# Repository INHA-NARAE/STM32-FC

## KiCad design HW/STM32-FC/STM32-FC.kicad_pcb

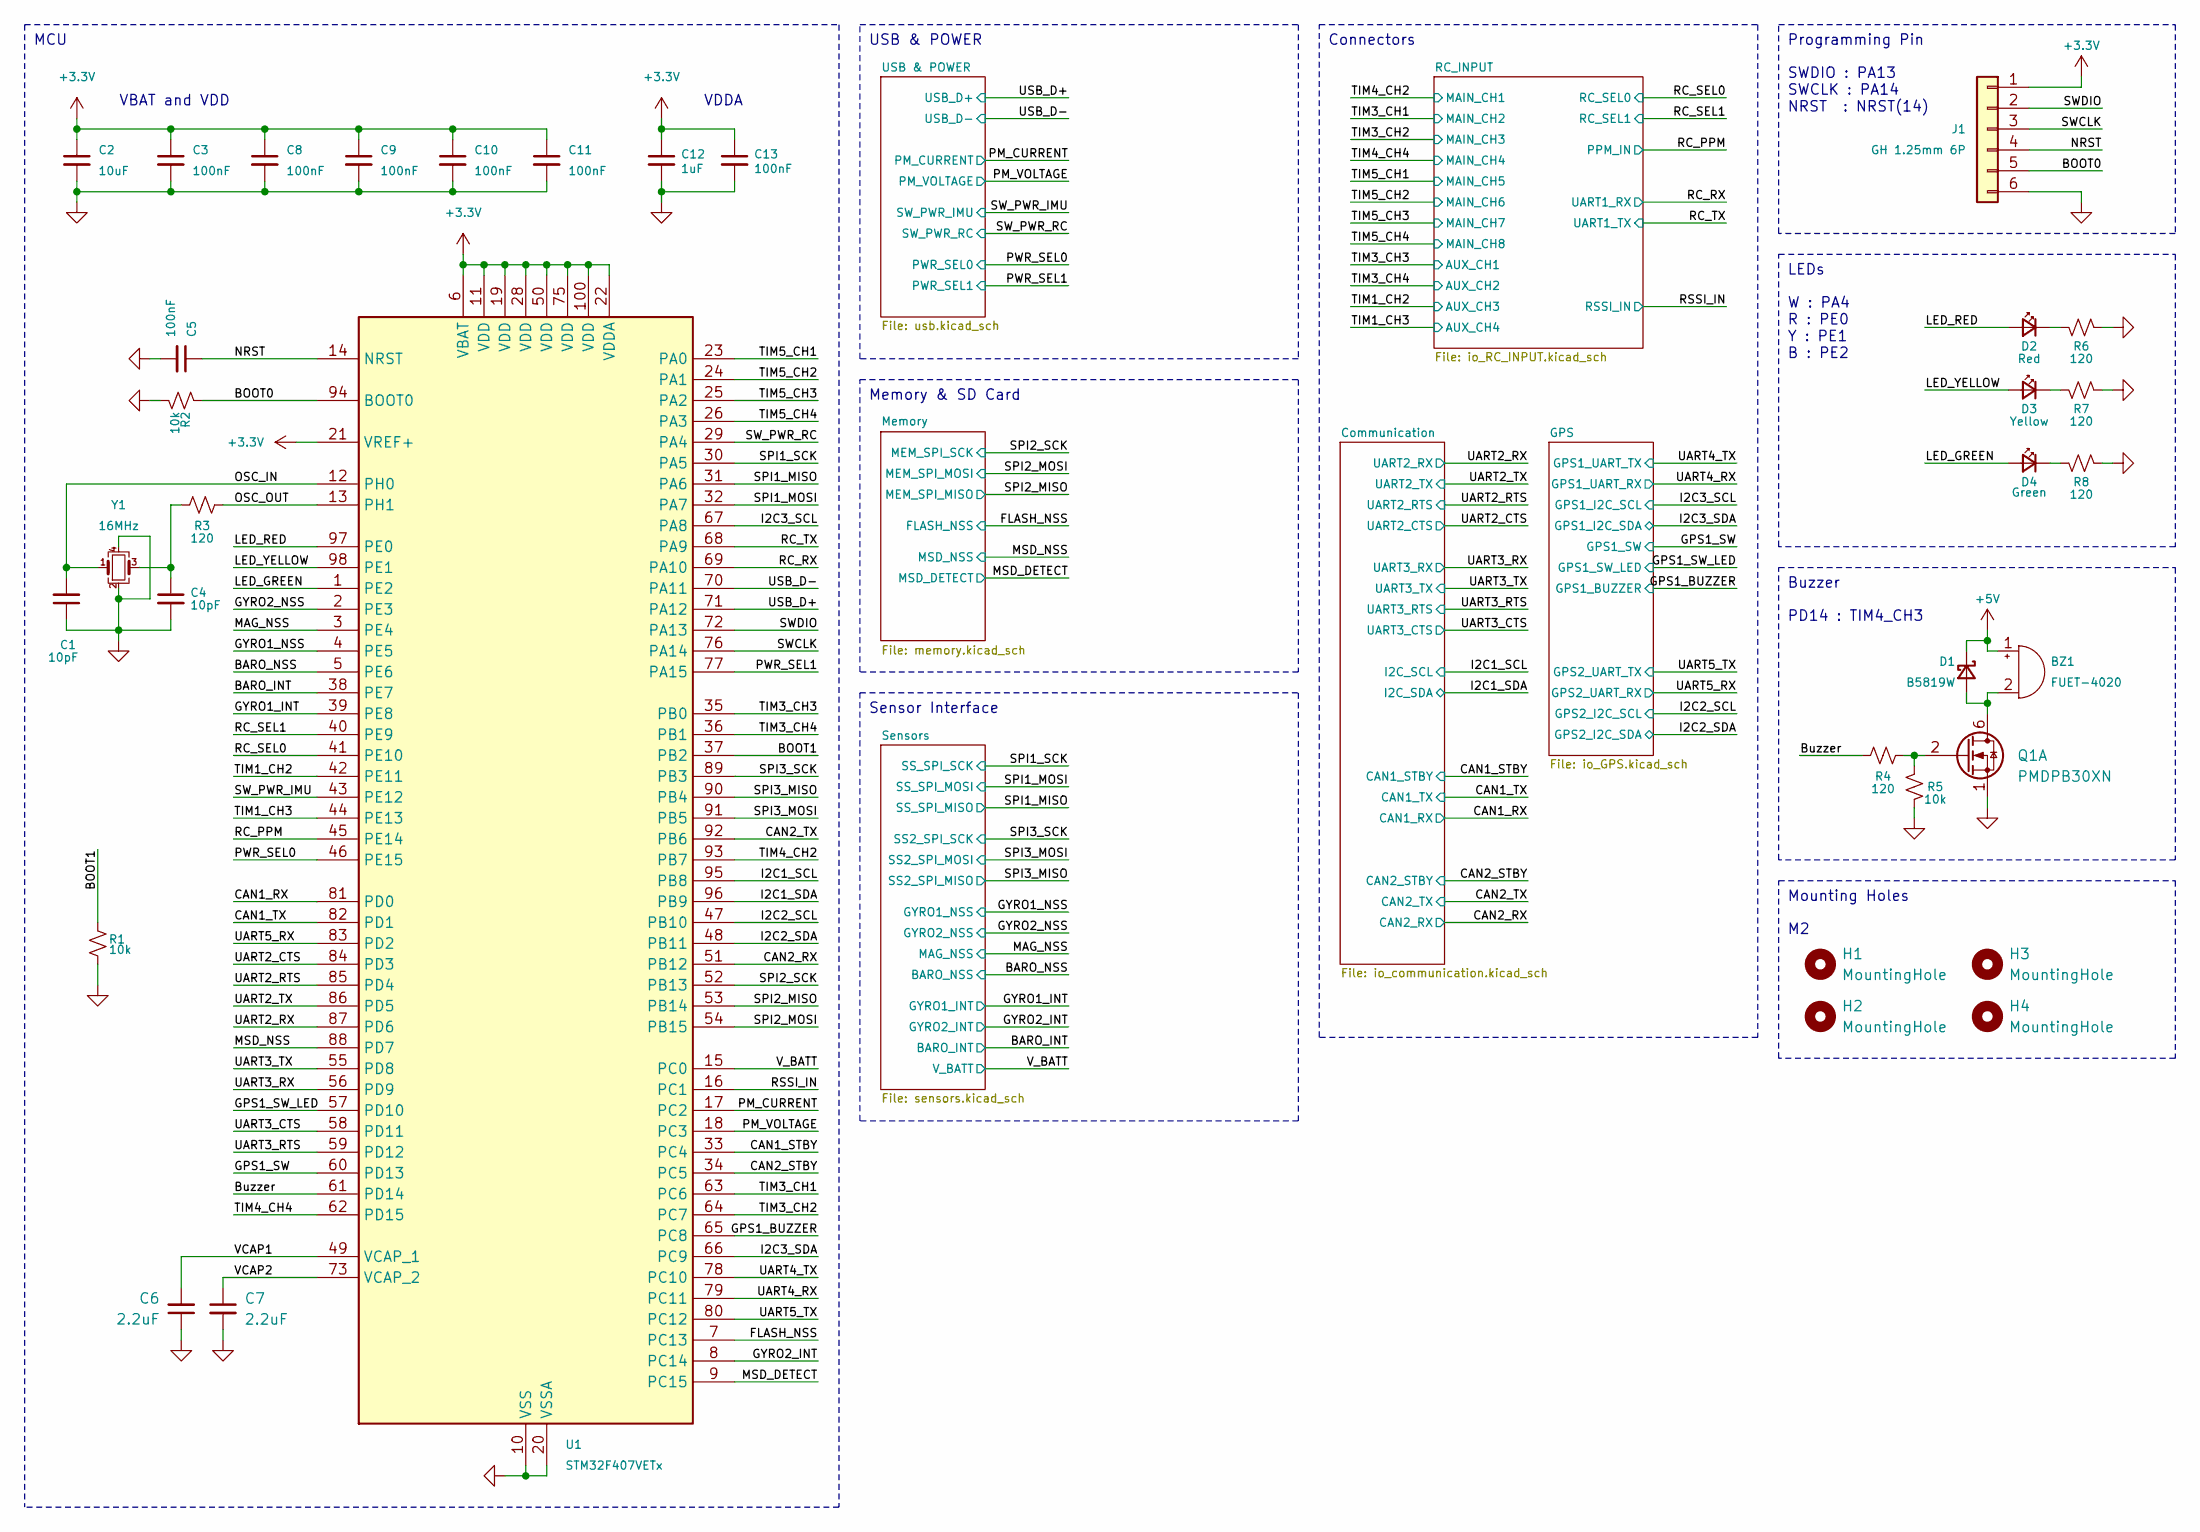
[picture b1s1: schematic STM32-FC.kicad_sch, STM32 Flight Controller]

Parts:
BZ1: FUET-4020; LCSC C391027
C1, C4: 10pF; C_0402_1005Metric; LCSC C1545
C2: 10uF; C_0402_1005Metric; LCSC C307415
C3, C5, C8, C9, C10, C11, C13: 100nF; C_0402_1005Metric; LCSC C1525
C6, C7: 2.2uF; C_0402_1005Metric; LCSC C170151
C12: 1uF; C_0402_1005Metric; LCSC C14445
D1: B5819W; D_SOD-323; LCSC C22624
D2: Red; LED_0402_1005Metric; LCSC C130719
D3: Yellow; LED_0402_1005Metric; LCSC C130721
D4: Green; LED_0402_1005Metric; LCSC C130722
H1, H2, H3, H4: MountingHole; MountingHole_2.2mm_M2
J1: GH 1.25mm 6P; JST_GH_SM06B-GHS-TB_06x1.25mm_Angled; LCSC C133065
Q1: PMDPB30XN; Nexperia_SOT1118; LCSC C478009
R1, R2, R5: 10k; R_0402_1005Metric; LCSC C25531
R3, R4, R6, R7, R8: 120; R_0402_1005Metric; LCSC C25079
U1: STM32F407VETx; LQFP-100_14x14mm_P0.5mm; LCSC C28730
Y1: 16MHz; Crystal_SMD_Abracon_ABM8G-4Pin_3.2x2.5mm; LCSC C1985423

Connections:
+3.3V: C2.1, C3.1, C8.1, C9.1, C10.1, C11.1, C12.1, C13.1, J1.1, U1.6 (VBAT), U1.11 (VDD), U1.19 (VDD), U1.21 (VREF+), U1.22 (VDDA), U1.28 (VDD), U1.50 (VDD), U1.75 (VDD), U1.100 (VDD); also elsewhere on the board
+5V: BZ1.1 (-), D1.1 (K); also elsewhere on the board
/BARO_INT: U1.38 (PE7); also elsewhere on the board
/BARO_NSS: U1.5 (PE6); also elsewhere on the board
/BOOT0: J1.5, R2.1, U1.94 (BOOT0)
/BOOT1: R1.1, U1.37 (PB2)
/Buzzer: R4.1, U1.61 (PD14)
/CAN1_RX: U1.81 (PD0); also elsewhere on the board
/CAN1_STBY: U1.33 (PC4); also elsewhere on the board
/CAN1_TX: U1.82 (PD1); also elsewhere on the board
/CAN2_RX: U1.51 (PB12); also elsewhere on the board
/CAN2_STBY: U1.34 (PC5); also elsewhere on the board
/CAN2_TX: U1.92 (PB6); also elsewhere on the board
/FLASH_NSS: U1.7 (PC13); also elsewhere on the board
/GPS1_BUZZER: U1.65 (PC8); also elsewhere on the board
/GPS1_SW: U1.60 (PD13); also elsewhere on the board
/GPS1_SW_LED: U1.57 (PD10); also elsewhere on the board
/GYRO1_INT: U1.39 (PE8); also elsewhere on the board
/GYRO1_NSS: U1.4 (PE5); also elsewhere on the board
/GYRO2_INT: U1.8 (PC14); also elsewhere on the board
/GYRO2_NSS: U1.2 (PE3); also elsewhere on the board
/I2C1_SCL: U1.95 (PB8); also elsewhere on the board
/I2C1_SDA: U1.96 (PB9); also elsewhere on the board
/I2C2_SCL: U1.47 (PB10); also elsewhere on the board
/I2C2_SDA: U1.48 (PB11); also elsewhere on the board
/I2C3_SCL: U1.67 (PA8); also elsewhere on the board
/I2C3_SDA: U1.66 (PC9); also elsewhere on the board
/LED_GREEN: D4.2 (A), U1.1 (PE2)
/LED_RED: D2.2 (A), U1.97 (PE0)
/LED_YELLOW: D3.2 (A), U1.98 (PE1)
/MAG_NSS: U1.3 (PE4); also elsewhere on the board
/MSD_DETECT: U1.9 (PC15); also elsewhere on the board
/MSD_NSS: U1.88 (PD7); also elsewhere on the board
/NRST: C5.1, J1.4, U1.14 (NRST)
/OSC_IN: C1.2, U1.12 (PH0), Y1.1
/OSC_OUT: R3.2, U1.13 (PH1)
/PM_CURRENT: U1.17 (PC2); also elsewhere on the board
/PM_VOLTAGE: U1.18 (PC3); also elsewhere on the board
/PWR_SEL0: U1.46 (PE15); also elsewhere on the board
/PWR_SEL1: U1.77 (PA15); also elsewhere on the board
/RC_PPM: U1.45 (PE14); also elsewhere on the board
/RC_RX: U1.69 (PA10); also elsewhere on the board
/RC_SEL0: U1.41 (PE10); also elsewhere on the board
/RC_SEL1: U1.40 (PE9); also elsewhere on the board
/RC_TX: U1.68 (PA9); also elsewhere on the board
/RSSI_IN: U1.16 (PC1); also elsewhere on the board
/SPI1_MISO: U1.31 (PA6); also elsewhere on the board
/SPI1_MOSI: U1.32 (PA7); also elsewhere on the board
/SPI1_SCK: U1.30 (PA5); also elsewhere on the board
/SPI2_MISO: U1.53 (PB14); also elsewhere on the board
/SPI2_MOSI: U1.54 (PB15); also elsewhere on the board
/SPI2_SCK: U1.52 (PB13); also elsewhere on the board
/SPI3_MISO: U1.90 (PB4); also elsewhere on the board
/SPI3_MOSI: U1.91 (PB5); also elsewhere on the board
/SPI3_SCK: U1.89 (PB3); also elsewhere on the board
/SWCLK: J1.3, U1.76 (PA14)
/SWDIO: J1.2, U1.72 (PA13)
/SW_PWR_IMU: U1.43 (PE12); also elsewhere on the board
/SW_PWR_RC: U1.29 (PA4); also elsewhere on the board
/TIM1_CH2: U1.42 (PE11); also elsewhere on the board
/TIM1_CH3: U1.44 (PE13); also elsewhere on the board
/TIM3_CH1: U1.63 (PC6); also elsewhere on the board
/TIM3_CH2: U1.64 (PC7); also elsewhere on the board
/TIM3_CH3: U1.35 (PB0); also elsewhere on the board
/TIM3_CH4: U1.36 (PB1); also elsewhere on the board
/TIM4_CH2: U1.93 (PB7); also elsewhere on the board
/TIM4_CH4: U1.62 (PD15); also elsewhere on the board
/TIM5_CH1: U1.23 (PA0); also elsewhere on the board
/TIM5_CH2: U1.24 (PA1); also elsewhere on the board
/TIM5_CH3: U1.25 (PA2); also elsewhere on the board
/TIM5_CH4: U1.26 (PA3); also elsewhere on the board
/UART2_CTS: U1.84 (PD3); also elsewhere on the board
/UART2_RTS: U1.85 (PD4); also elsewhere on the board
/UART2_RX: U1.87 (PD6); also elsewhere on the board
/UART2_TX: U1.86 (PD5); also elsewhere on the board
/UART3_CTS: U1.58 (PD11); also elsewhere on the board
/UART3_RTS: U1.59 (PD12); also elsewhere on the board
/UART3_RX: U1.56 (PD9); also elsewhere on the board
/UART3_TX: U1.55 (PD8); also elsewhere on the board
/UART4_RX: U1.79 (PC11); also elsewhere on the board
/UART4_TX: U1.78 (PC10); also elsewhere on the board
/UART5_RX: U1.83 (PD2); also elsewhere on the board
/UART5_TX: U1.80 (PC12); also elsewhere on the board
/USB_D+: U1.71 (PA12); also elsewhere on the board
/USB_D-: U1.70 (PA11); also elsewhere on the board
/VCAP1: C6.2, U1.49 (VCAP_1)
/VCAP2: C7.1, U1.73 (VCAP_2)
/V_BATT: U1.15 (PC0); also elsewhere on the board
unnamed: BZ1.2 (+), D1.2 (A), Q1.6 (D), Q1.7 (D)
unnamed: C4.1, R3.1, Y1.3
unnamed: D2.1 (K), R6.1
unnamed: D3.1 (K), R7.1
unnamed: D4.1 (K), R8.1
unnamed: Q1.2 (G), R4.2, R5.1

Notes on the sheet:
Connectors
PD14 : TIM4_CH3
MCU
VDDA
Buzzer
Sensor Interface
LEDs
Programming Pin
Memory & SD Card
USB & POWER
W : PA4 R : PE0 Y : PE1 B : PE2
SWDIO : PA13 SWCLK : PA14 NRST : NRST(14)
VBAT and VDD
Mounting Holes

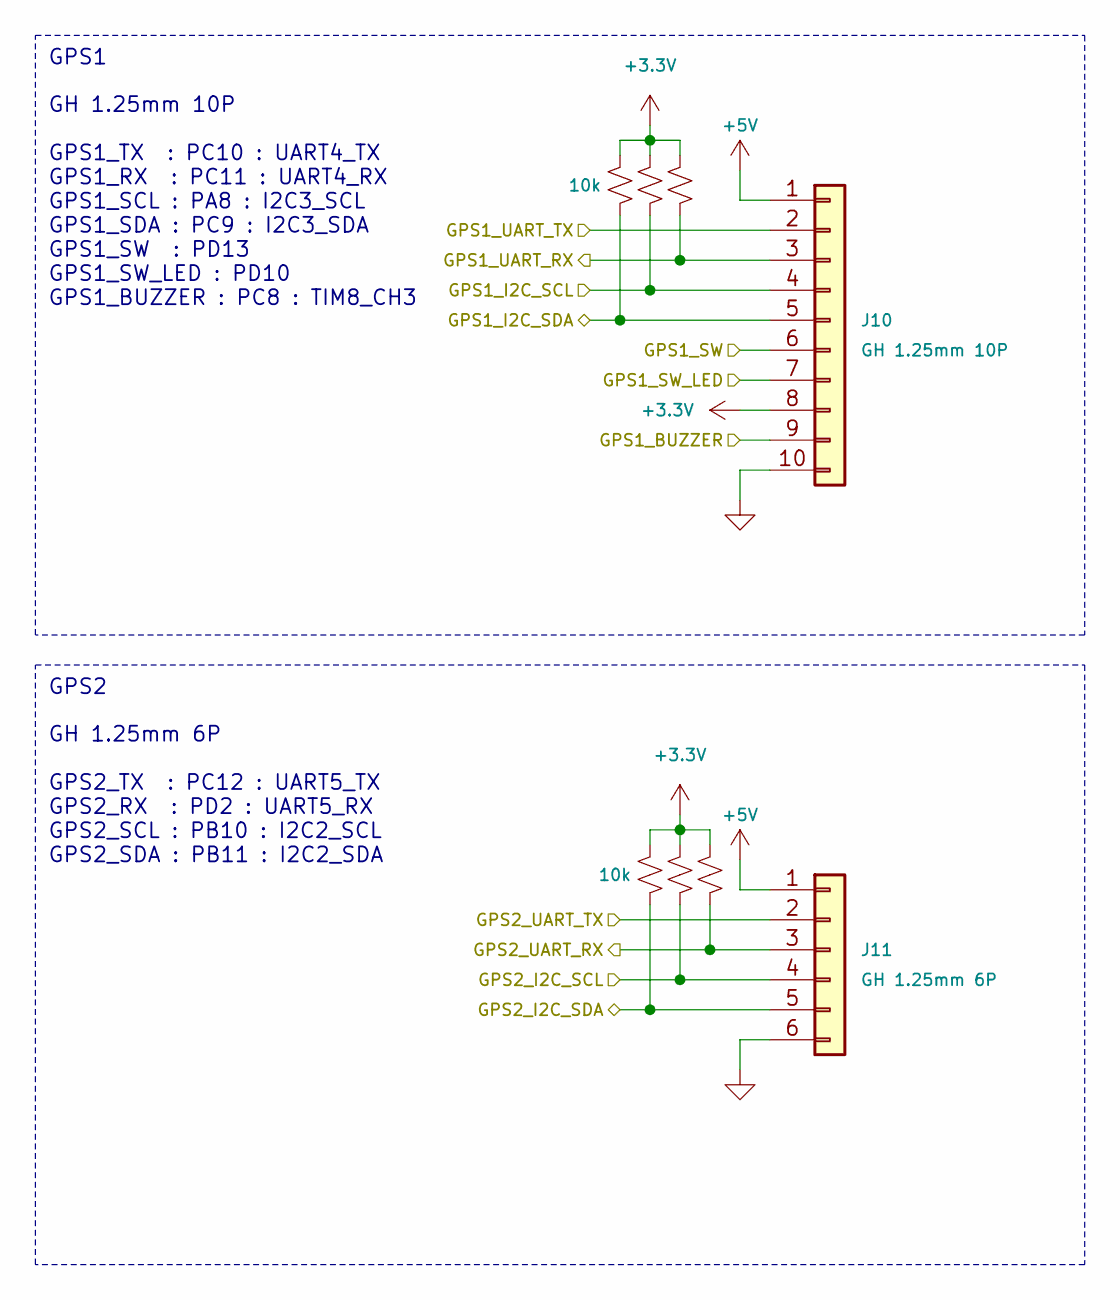
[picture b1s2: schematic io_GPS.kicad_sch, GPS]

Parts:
J10: GH 1.25mm 10P; JST_GH_SM10B-GHS-TB_10x1.25mm_Angled; LCSC C2683602
J11: GH 1.25mm 6P; JST_GH_SM06B-GHS-TB_06x1.25mm_Angled; LCSC C133065
R38, R39, R40, R41, R42, R43: 10k; R_0402_1005Metric; LCSC C25531

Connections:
+3.3V: J10.8, R38.1, R39.1, R40.1, R41.1, R42.1, R43.1; also elsewhere on the board
+5V: J10.1, J11.1; also elsewhere on the board
/GPS1_BUZZER: J10.9; also elsewhere on the board
/GPS1_SW: J10.6; also elsewhere on the board
/GPS1_SW_LED: J10.7; also elsewhere on the board
/I2C2_SCL: J11.4, R42.2; also elsewhere on the board
/I2C2_SDA: J11.5, R40.2; also elsewhere on the board
/I2C3_SCL: J10.4, R39.2; also elsewhere on the board
/I2C3_SDA: J10.5, R38.2; also elsewhere on the board
/UART4_RX: J10.3, R41.2; also elsewhere on the board
/UART4_TX: J10.2; also elsewhere on the board
/UART5_RX: J11.3, R43.2; also elsewhere on the board
/UART5_TX: J11.2; also elsewhere on the board

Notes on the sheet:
GH 1.25mm 10P GPS1_TX : PC10 : UART4_TX GPS1_RX : PC11 : UART4_RX GPS1_SCL : PA8 : I2C3_SCL GPS1_SDA : PC9 : I2C3_SDA GPS1_SW : PD13 GPS1_SW_LED : PD10 GPS1_BUZZER : PC8 : TIM8_CH3
GH 1.25mm 6P GPS2_TX : PC12 : UART5_TX GPS2_RX : PD2 : UART5_RX GPS2_SCL : PB10 : I2C2_SCL GPS2_SDA : PB11 : I2C2_SDA
GPS2
GPS1

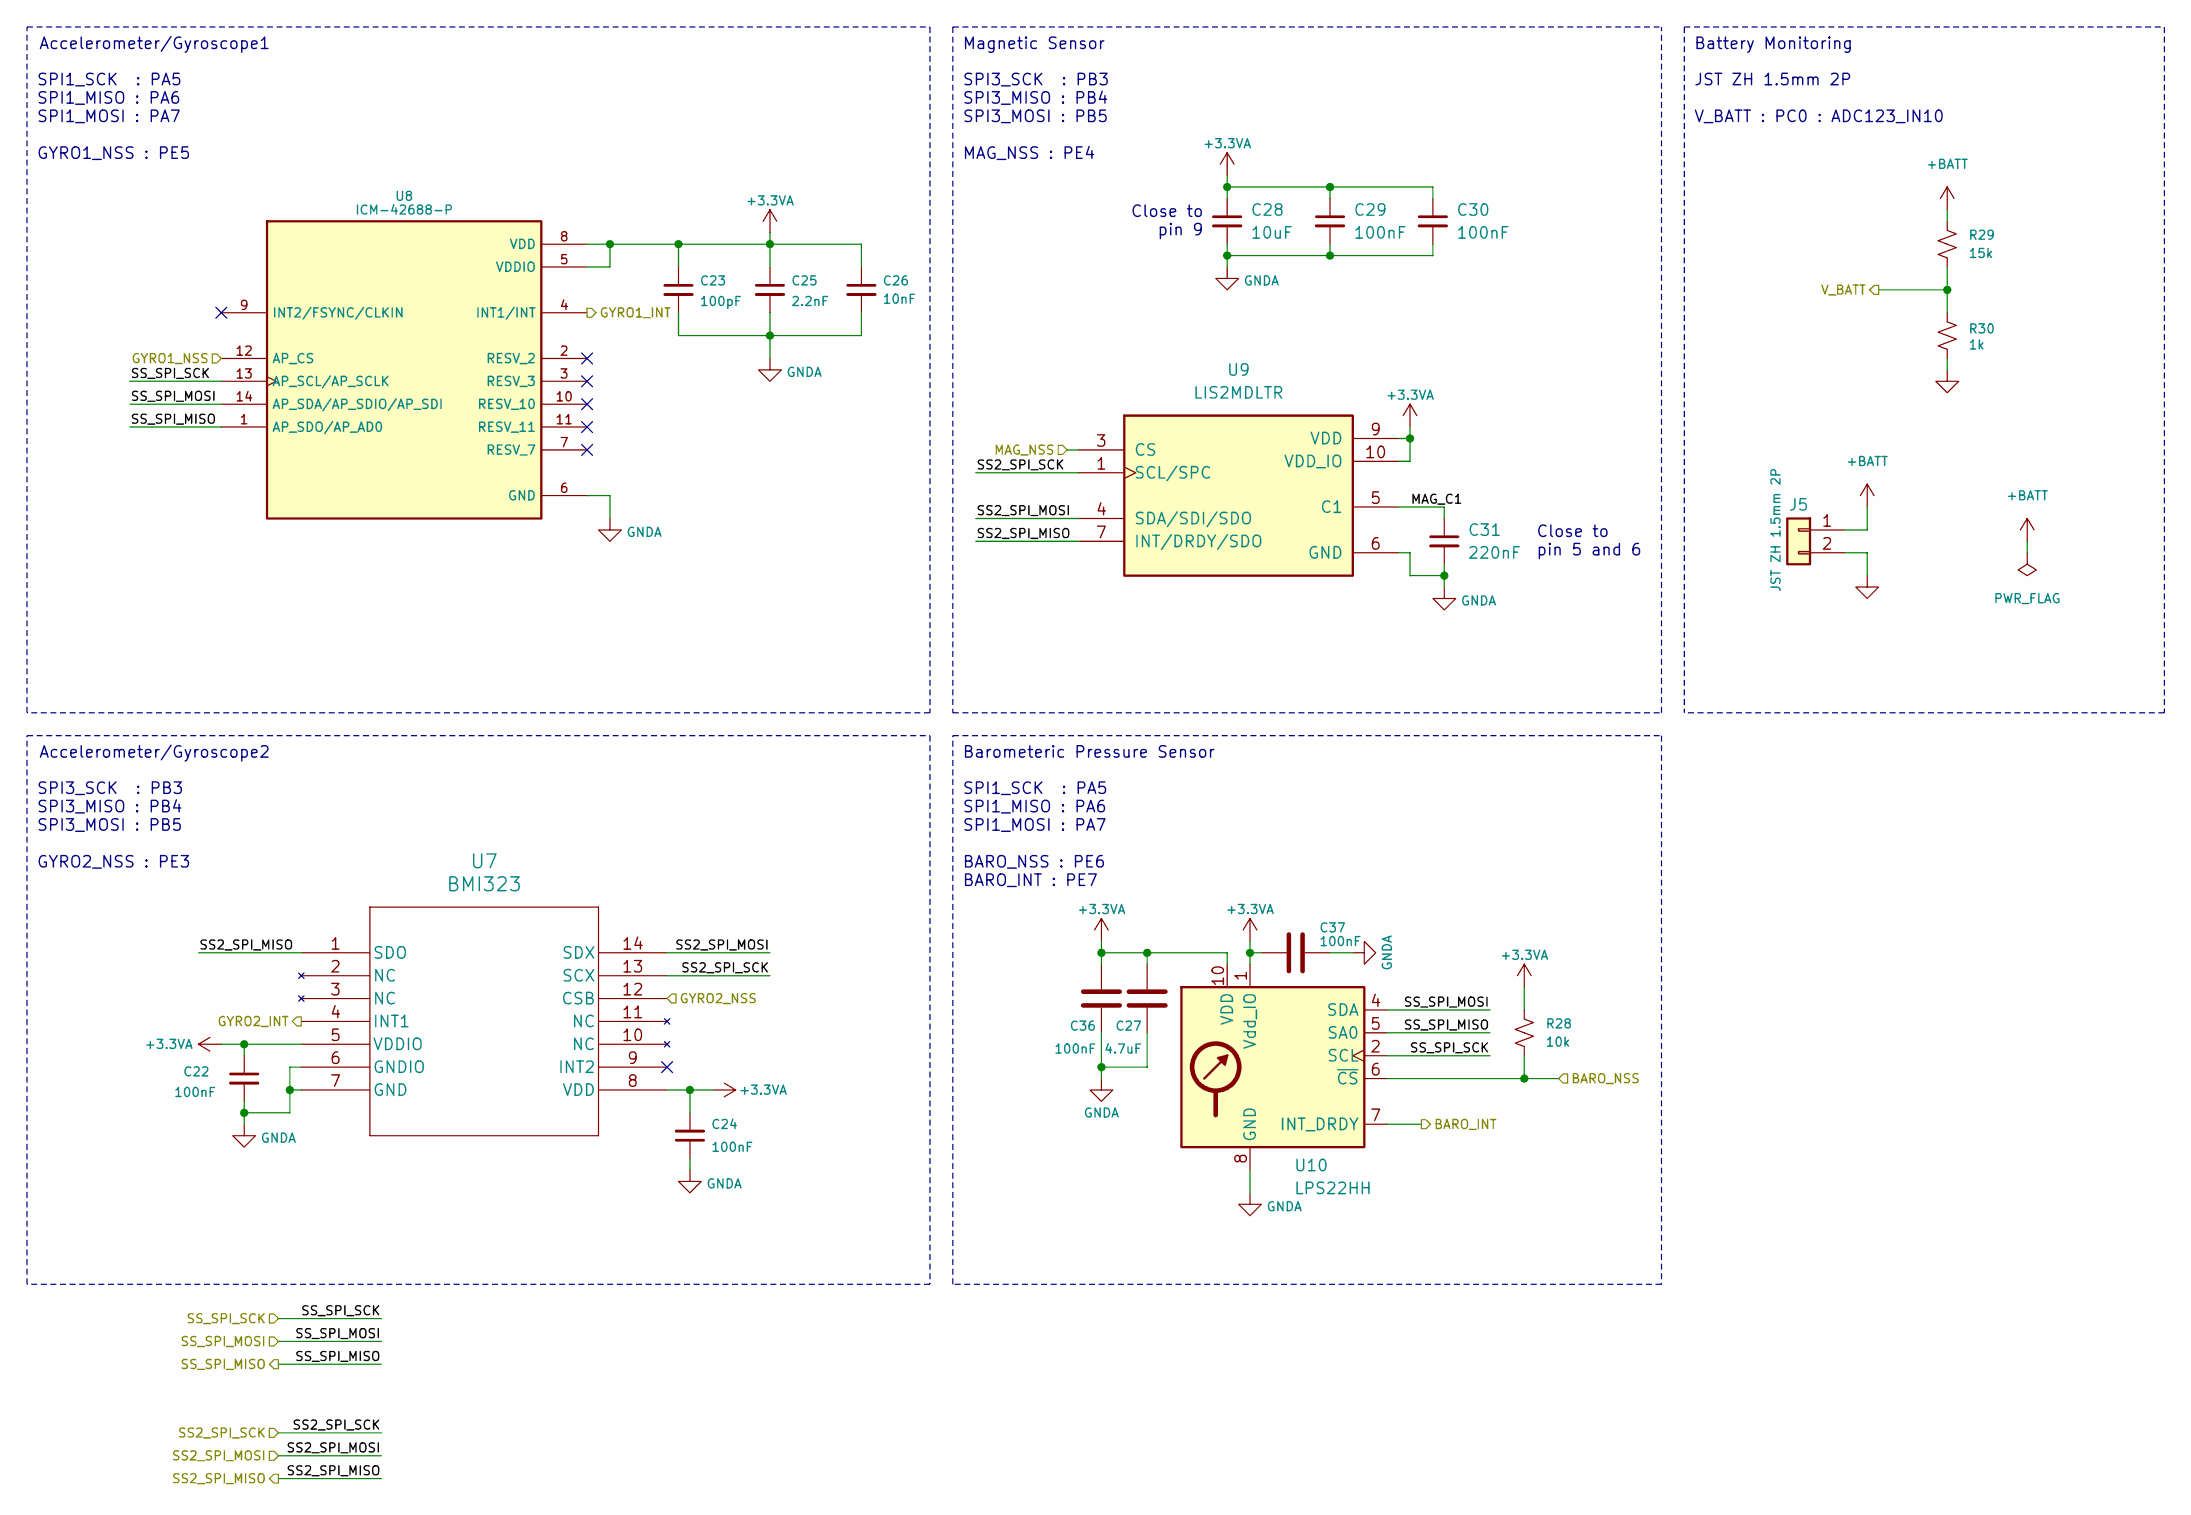
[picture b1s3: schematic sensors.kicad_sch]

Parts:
C22, C24, C29, C30: 100nF; C_0402_1005Metric; LCSC C1525
C23: 100pF; C_0402_1005Metric; LCSC C152819
C25: 2.2nF; C_0402_1005Metric; LCSC C84703
C26: 10nF; C_0402_1005Metric; LCSC C15195
C27: 4.7uF; C_0402_1005Metric; LCSC C307423
C28: 10uF; C_0402_1005Metric; LCSC C307415
C31: 220nF; C_0402_1005Metric; LCSC C16651
C36, C37: 100nF; C_0402_1005Metric; LCSC C307423
J5: JST ZH 1.5mm 2P; JST_ZH_S2B-ZR-SM4A-TF_1x02-1MP_P1.50mm_Horizontal; LCSC C265329
R28: 10k; R_0402_1005Metric; LCSC C25531
R29: 15k; R_0402_1005Metric; LCSC C25539
R30: 1k; R_0402_1005Metric; LCSC C106235
U7: BMI323; BMI323_L; LCSC C5368700
U8: ICM-42688-P; IIM42352_L; LCSC C1850418
U9: LIS2MDLTR; PARTREV Rev 5; LCSC C919695
U10: LPS22HH; ST_HLGA-10_2x2mm_P0.5mm_LayoutBorder3x2y; LCSC C2827824

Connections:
+3.3VA: C22.1, C23.1, C24.2, C25.1, C26.1, C27.2, C28.1, C29.1, C30.1, C36.2, C37.2, R28.1, U7.5 (VDDIO), U7.8 (VDD), U8.5 (VDDIO), U8.8 (VDD), U9.9 (VDD), U9.10 (VDD_IO), U10.1 (Vdd_IO), U10.10 (VDD); also elsewhere on the board
+BATT: J5.1, R29.1
/BARO_INT: U10.7 (INT_DRDY); also elsewhere on the board
/BARO_NSS: R28.2, U10.6 (~CS); also elsewhere on the board
/GYRO1_INT: U8.4 (INT1/INT); also elsewhere on the board
/GYRO1_NSS: U8.12 (AP_CS); also elsewhere on the board
/GYRO2_INT: U7.4 (INT1); also elsewhere on the board
/GYRO2_NSS: U7.12 (CSB); also elsewhere on the board
/MAG_NSS: U9.3 (CS); also elsewhere on the board
/SPI1_MISO: U8.1 (AP_SDO/AP_AD0), U10.5 (SA0); also elsewhere on the board
/SPI1_MOSI: U8.14 (AP_SDA/AP_SDIO/AP_SDI), U10.4 (SDA); also elsewhere on the board
/SPI1_SCK: U8.13 (AP_SCL/AP_SCLK), U10.2 (SCL); also elsewhere on the board
/SPI3_MISO: U7.1 (SDO), U9.7 (INT/DRDY/SDO); also elsewhere on the board
/SPI3_MOSI: U7.14 (SDX), U9.4 (SDA/SDI/SDO); also elsewhere on the board
/SPI3_SCK: U7.13 (SCX), U9.1 (SCL/SPC); also elsewhere on the board
/Sensors/MAG_C1: C31.1, U9.5 (C1)
/V_BATT: R29.2, R30.1; also elsewhere on the board

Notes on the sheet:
Close to pin 9
Magnetic Sensor
Barometeric Pressure Sensor
Battery Monitoring
Accelerometer/Gyroscope1
SPI3_SCK : PB3 SPI3_MISO : PB4 SPI3_MOSI : PB5 GYRO2_NSS : PE3
SPI1_SCK : PA5 SPI1_MISO : PA6 SPI1_MOSI : PA7 BARO_NSS : PE6 BARO_INT : PE7
JST ZH 1.5mm 2P V_BATT : PC0 : ADC123_IN10
SPI1_SCK : PA5 SPI1_MISO : PA6 SPI1_MOSI : PA7 GYRO1_NSS : PE5
Accelerometer/Gyroscope2
Close to pin 5 and 6
SPI3_SCK : PB3 SPI3_MISO : PB4 SPI3_MOSI : PB5 MAG_NSS : PE4

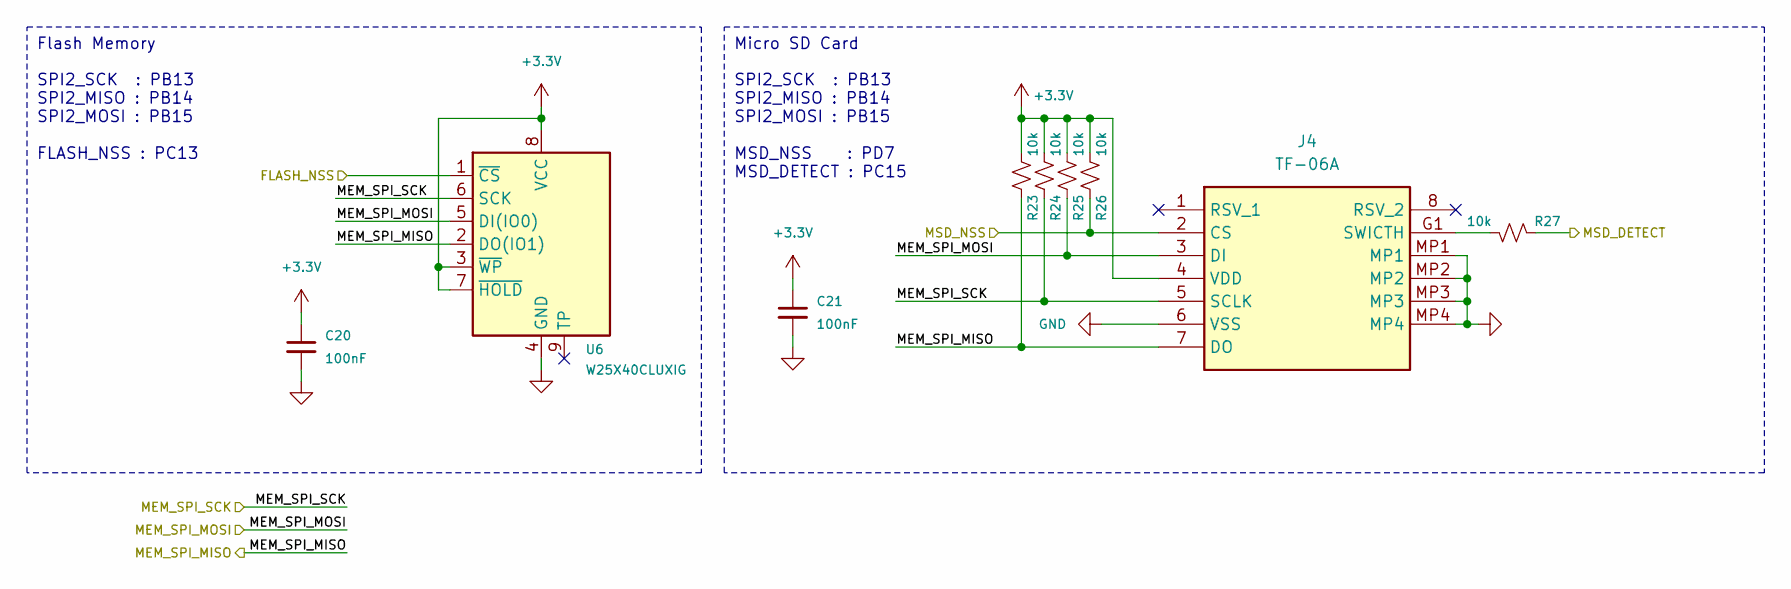
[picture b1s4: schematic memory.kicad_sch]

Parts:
C20, C21: 100nF; C_0402_1005Metric; LCSC C1525
J4: TF-06A; TF06A; Manufacturer_Part_Number TF-06A; LCSC C693844
R23, R24, R25, R26, R27: 10k; R_0402_1005Metric; LCSC C25531
U6: W25X40CLUXIG; USON_LUXIG TR_WIN-L; LCSC C401661

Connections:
+3.3V: C20.1, C21.1, J4.4 (VDD), R23.1, R24.1, R25.1, R26.1, U6.3 (~WP), U6.7 (~HOLD), U6.8 (VCC); also elsewhere on the board
/FLASH_NSS: U6.1 (~CS); also elsewhere on the board
/MSD_DETECT: R27.1; also elsewhere on the board
/MSD_NSS: J4.2 (CS), R26.2; also elsewhere on the board
/SPI2_MISO: J4.7 (DO), R23.2, U6.2 (DO(IO1)); also elsewhere on the board
/SPI2_MOSI: J4.3 (DI), R25.2, U6.5 (DI(IO0)); also elsewhere on the board
/SPI2_SCK: J4.5 (SCLK), R24.2, U6.6 (SCK); also elsewhere on the board
unnamed: J4.G1 (SWICTH), R27.2

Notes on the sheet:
Micro SD Card
SPI2_SCK : PB13 SPI2_MISO : PB14 SPI2_MOSI : PB15 FLASH_NSS : PC13
Flash Memory
SPI2_SCK : PB13 SPI2_MISO : PB14 SPI2_MOSI : PB15 MSD_NSS : PD7 MSD_DETECT : PC15

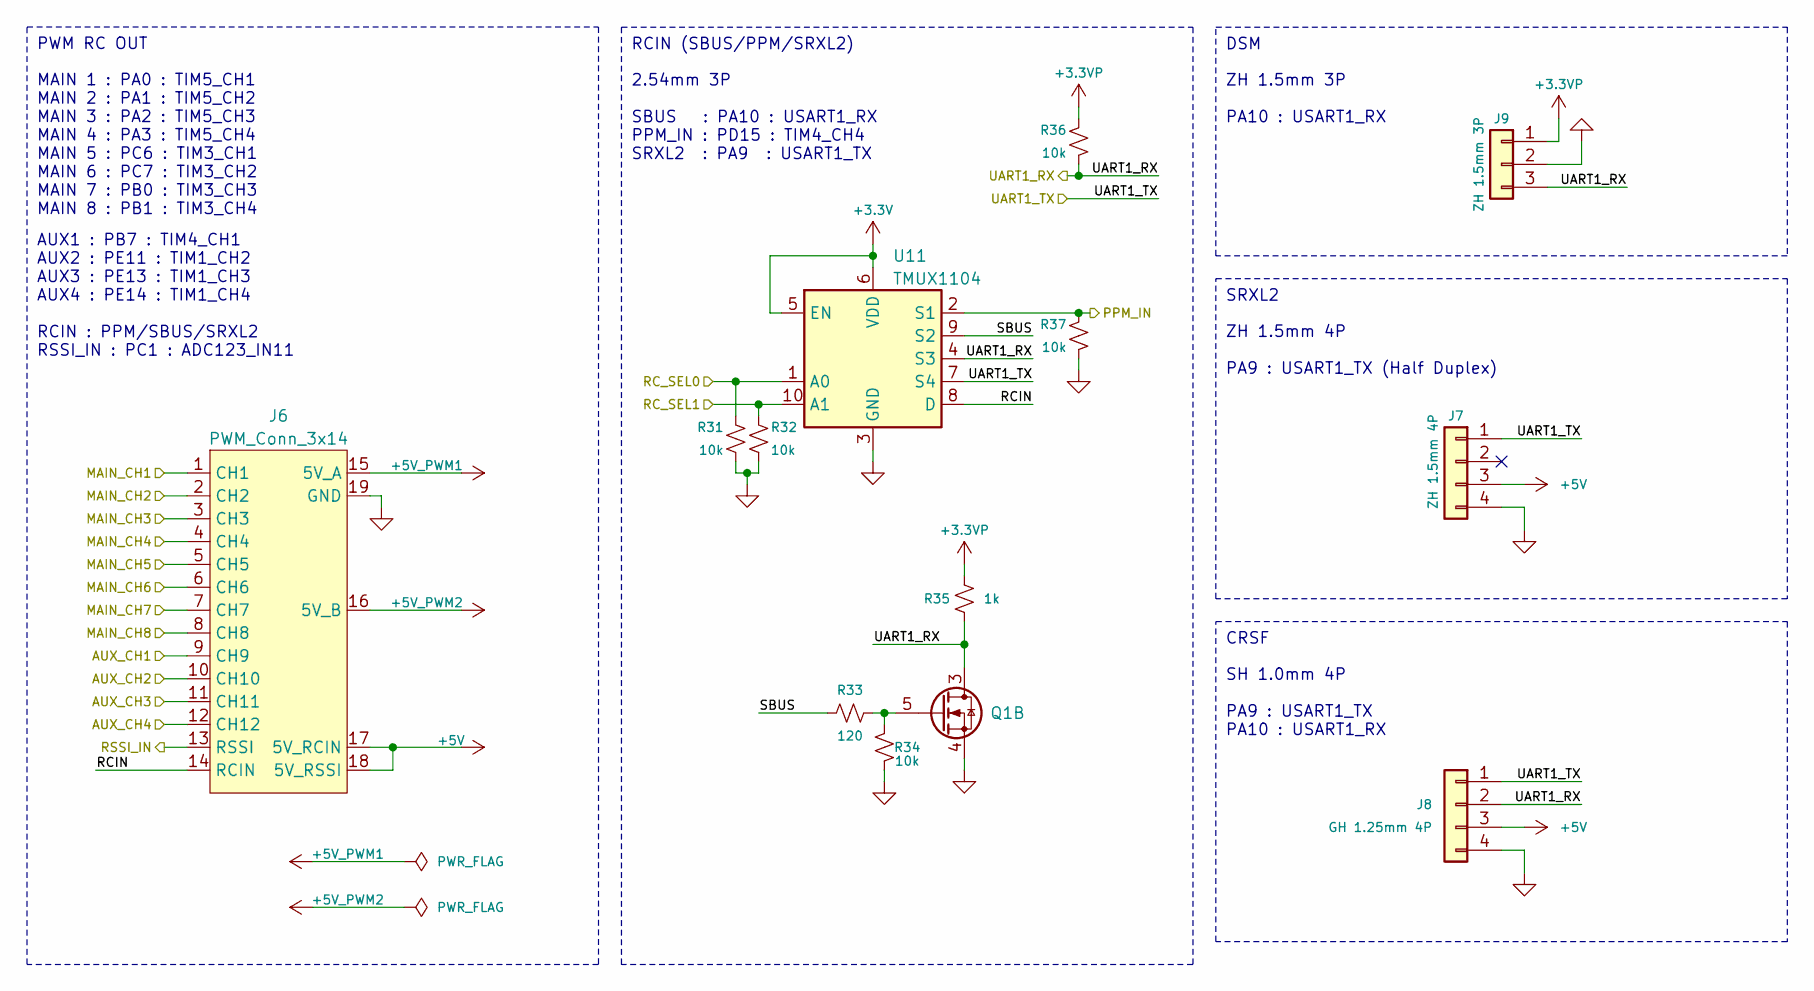
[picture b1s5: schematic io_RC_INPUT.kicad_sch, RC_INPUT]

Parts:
J6: PWM_Conn_3x14; LCSC C3327492
J7: ZH 1.5mm 4P; JST_ZH_S4B-ZR-SM4A-TF_1x04-1MP_P1.50mm_Horizontal; LCSC C485354
J8: GH 1.25mm 4P; JST_GH_SM04B-GHS-TB_04x1.25mm_Angled; LCSC C189895
J9: ZH 1.5mm 3P; JST_ZH_S3B-ZR-SM4A-TF_1x03-1MP_P1.50mm_Horizontal; LCSC C72591
Q1: PMDPB30XN; Nexperia_SOT1118; LCSC C478009
R31, R32, R34, R36, R37: 10k; R_0402_1005Metric; LCSC C25531
R33: 120; R_0402_1005Metric; LCSC C25079
R35: 1k; R_0402_1005Metric; LCSC C106235
U11: TMUX1104; LCSC C2865387

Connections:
+3.3V: U11.5 (EN), U11.6 (VDD); also elsewhere on the board
+3.3VP: J9.1, R35.1, R36.1; also elsewhere on the board
+5V: J6.17 (5V_RCIN), J6.18 (5V_RSSI), J7.3, J8.3; also elsewhere on the board
+5V_PWM1: J6.15 (5V_A); also elsewhere on the board
+5V_PWM2: J6.16 (5V_B); also elsewhere on the board
/RC_INPUT/RCIN: J6.14 (RCIN), U11.8 (D)
/RC_INPUT/SBUS: R33.1, U11.9 (S2)
/RC_PPM: R37.1, U11.2 (S1); also elsewhere on the board
/RC_RX: J8.2, J9.3, Q1.3 (D), Q1.8 (D), R35.2, R36.2, U11.4 (S3); also elsewhere on the board
/RC_SEL0: R31.1, U11.1 (A0); also elsewhere on the board
/RC_SEL1: R32.1, U11.10 (A1); also elsewhere on the board
/RC_TX: J7.1, J8.1, U11.7 (S4); also elsewhere on the board
/RSSI_IN: J6.13 (RSSI); also elsewhere on the board
/TIM1_CH2: J6.11 (CH11); also elsewhere on the board
/TIM1_CH3: J6.12 (CH12); also elsewhere on the board
/TIM3_CH1: J6.2 (CH2); also elsewhere on the board
/TIM3_CH2: J6.3 (CH3); also elsewhere on the board
/TIM3_CH3: J6.9 (CH9); also elsewhere on the board
/TIM3_CH4: J6.10 (CH10); also elsewhere on the board
/TIM4_CH2: J6.1 (CH1); also elsewhere on the board
/TIM4_CH4: J6.4 (CH4); also elsewhere on the board
/TIM5_CH1: J6.5 (CH5); also elsewhere on the board
/TIM5_CH2: J6.6 (CH6); also elsewhere on the board
/TIM5_CH3: J6.7 (CH7); also elsewhere on the board
/TIM5_CH4: J6.8 (CH8); also elsewhere on the board
unnamed: Q1.5 (G), R33.2, R34.1

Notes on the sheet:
CRSF
RCIN (SBUS/PPM/SRXL2)
ZH 1.5mm 3P PA10 : USART1_RX
SRXL2
2.54mm 3P SBUS : PA10 : USART1_RX PPM_IN : PD15 : TIM4_CH4 SRXL2 : PA9 : USART1_TX
SH 1.0mm 4P PA9 : USART1_TX PA10 : USART1_RX
DSM
MAIN 1 : PA0 : TIM5_CH1 MAIN 2 : PA1 : TIM5_CH2 MAIN 3 : PA2 : TIM5_CH3 MAIN 4 : PA3 : TIM5_CH4 MAIN 5 : PC6 : TIM3_CH1 MAIN 6 : PC7 : TIM3_CH2 MAIN 7 : PB0 : TIM3_CH3 MAIN 8 : PB1 : TIM3_CH4
PWM RC OUT
AUX1 : PB7 : TIM4_CH1 AUX2 : PE11 : TIM1_CH2 AUX3 : PE13 : TIM1_CH3 AUX4 : PE14 : TIM1_CH4 RCIN : PPM/SBUS/SRXL2 RSSI_IN : PC1 : ADC123_IN11
ZH 1.5mm 4P PA9 : USART1_TX (Half Duplex)

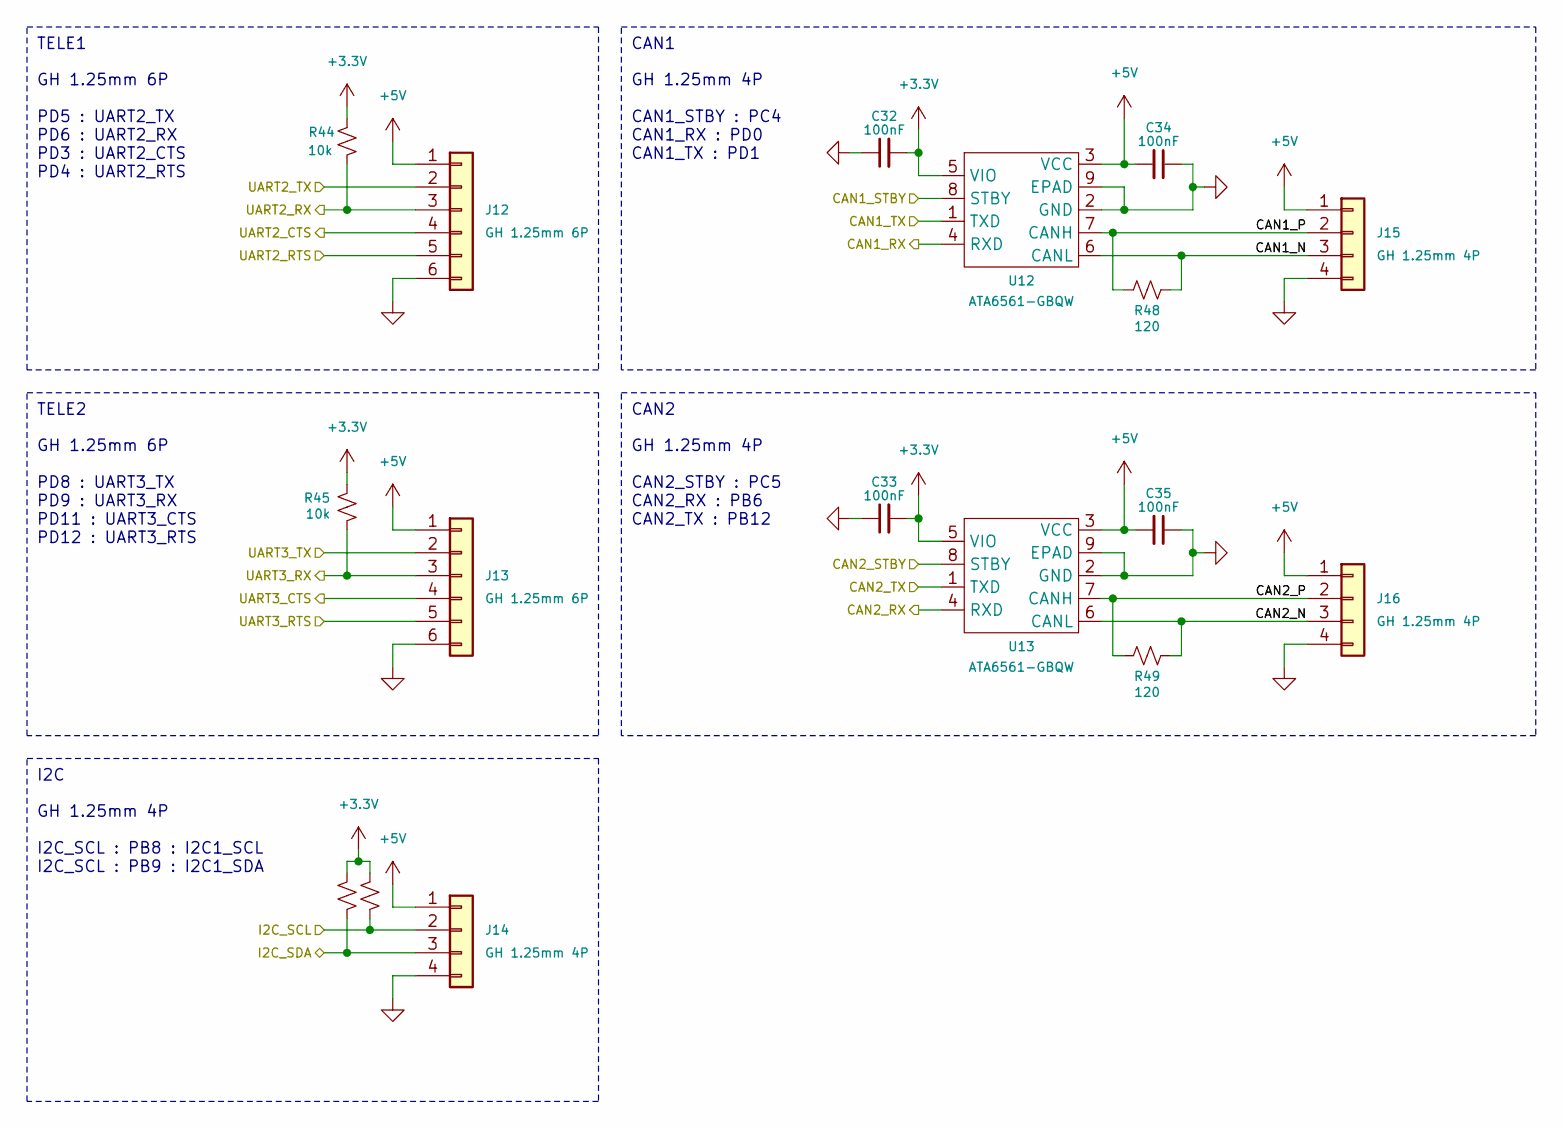
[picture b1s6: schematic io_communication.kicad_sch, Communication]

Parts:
C32, C33, C34, C35: 100nF; C_0402_1005Metric; LCSC C1525
J12, J13: GH 1.25mm 6P; JST_GH_SM06B-GHS-TB_06x1.25mm_Angled; LCSC C133065
J14, J15, J16: GH 1.25mm 4P; JST_GH_SM04B-GHS-TB_04x1.25mm_Angled; LCSC C189895
R44, R45, R46, R47: 10k; R_0402_1005Metric; LCSC C25531
R48, R49: 120; R_0402_1005Metric; LCSC C25079
U12, U13: ATA6561-GBQW; VDFN8_3X3_MCH-L; LCSC C617297

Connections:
+3.3V: C32.2, C33.2, R44.1, R45.1, R46.1, R47.1, U12.5 (VIO), U13.5 (VIO); also elsewhere on the board
+5V: C34.2, C35.2, J12.1, J13.1, J14.1, J15.1, J16.1, U12.3 (VCC), U13.3 (VCC); also elsewhere on the board
/CAN1_RX: U12.4 (RXD); also elsewhere on the board
/CAN1_STBY: U12.8 (STBY); also elsewhere on the board
/CAN1_TX: U12.1 (TXD); also elsewhere on the board
/CAN2_RX: U13.4 (RXD); also elsewhere on the board
/CAN2_STBY: U13.8 (STBY); also elsewhere on the board
/CAN2_TX: U13.1 (TXD); also elsewhere on the board
/Communication/CAN1_N: J15.3, R48.2, U12.6 (CANL)
/Communication/CAN1_P: J15.2, R48.1, U12.7 (CANH)
/Communication/CAN2_N: J16.3, R49.2, U13.6 (CANL)
/Communication/CAN2_P: J16.2, R49.1, U13.7 (CANH)
/I2C1_SCL: J14.2, R47.2; also elsewhere on the board
/I2C1_SDA: J14.3, R46.2; also elsewhere on the board
/UART2_CTS: J12.4; also elsewhere on the board
/UART2_RTS: J12.5; also elsewhere on the board
/UART2_RX: J12.3, R44.2; also elsewhere on the board
/UART2_TX: J12.2; also elsewhere on the board
/UART3_CTS: J13.4; also elsewhere on the board
/UART3_RTS: J13.5; also elsewhere on the board
/UART3_RX: J13.3, R45.2; also elsewhere on the board
/UART3_TX: J13.2; also elsewhere on the board

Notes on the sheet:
CAN2
GH 1.25mm 4P CAN2_STBY : PC5 CAN2_RX : PB6 CAN2_TX : PB12
GH 1.25mm 4P CAN1_STBY : PC4 CAN1_RX : PD0 CAN1_TX : PD1
TELE1
CAN1
GH 1.25mm 6P PD5 : UART2_TX PD6 : UART2_RX PD3 : UART2_CTS PD4 : UART2_RTS
GH 1.25mm 6P PD8 : UART3_TX PD9 : UART3_RX PD11 : UART3_CTS PD12 : UART3_RTS
I2C
GH 1.25mm 4P I2C_SCL : PB8 : I2C1_SCL I2C_SCL : PB9 : I2C1_SDA
TELE2

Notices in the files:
SW/Plane/Core/Src/main.c:
Copyright (c) 2025 STMicroelectronics.
All rights reserved.
This software is licensed under terms that can be found in the LICENSE file
